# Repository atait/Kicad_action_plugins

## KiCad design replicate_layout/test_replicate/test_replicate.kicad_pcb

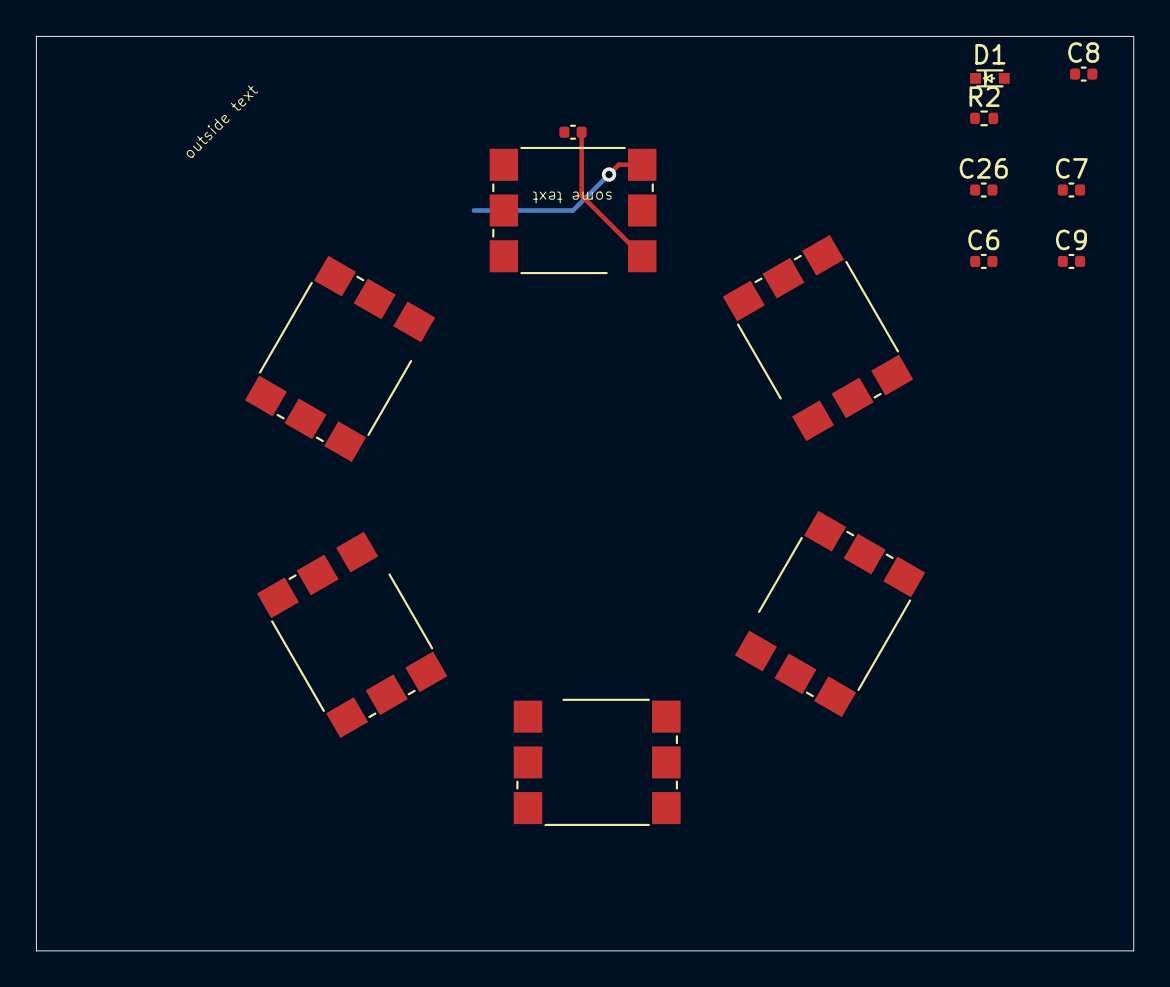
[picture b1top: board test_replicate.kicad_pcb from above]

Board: 4 copper layers, 61.0 x 50.8 mm, 14 parts (0 on the bottom side), 13 nets.

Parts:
C2, C6, C7, C8, C9, C26: 100nF; C_0402_1005Metric
D1: D,1N4148WT; D_SOD-523_withFiducial
R2: 1kΩ; R_0402_1005Metric
SW1, SW2, SW3, SW4, SW5, SW6: SW_DIP_x03; Pulse_PA2004NL

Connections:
+5V: C2.2, C6.2, C7.2, C8.2, C9.2, C26.2, R2.2, SW1.1, SW2.1, SW3.1, SW4.1, SW5.1, SW6.1
/SWs1/BO: SW2.3, SW6.5
/SWs1/DO: SW2.2, SW6.6
/SWs2/BO: SW2.5, SW5.3
/SWs2/DO: SW2.6, SW5.2
/SWs3/BO: SW4.3, SW5.5
/SWs3/DO: SW4.2, SW5.6
/SWs4/BO: SW3.3, SW4.5
/SWs4/DO: SW3.2, SW4.6
/SWs/BO: SW1.5, SW6.3
/SWs/DI: D1.1 (K), R2.1, SW1.2
/SWs/DO: SW1.6, SW6.2
GND: C2.1, C6.1, C7.1, C8.1, C9.1, C26.1, D1.2 (A), SW1.4, SW2.4, SW3.4, SW4.4, SW5.4, SW6.4

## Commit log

2023-05-14 Printing any exceptions for the user
2023-05-14 patching vector/rect for v7
2023-05-14 v7 and v6 compatible Duplicate
2023-05-14 v7 compatible Rotate, if v6 Rotate fails
2023-05-14 prevent double removal if v7
2023-05-14 New tester PCB using most replicate features
